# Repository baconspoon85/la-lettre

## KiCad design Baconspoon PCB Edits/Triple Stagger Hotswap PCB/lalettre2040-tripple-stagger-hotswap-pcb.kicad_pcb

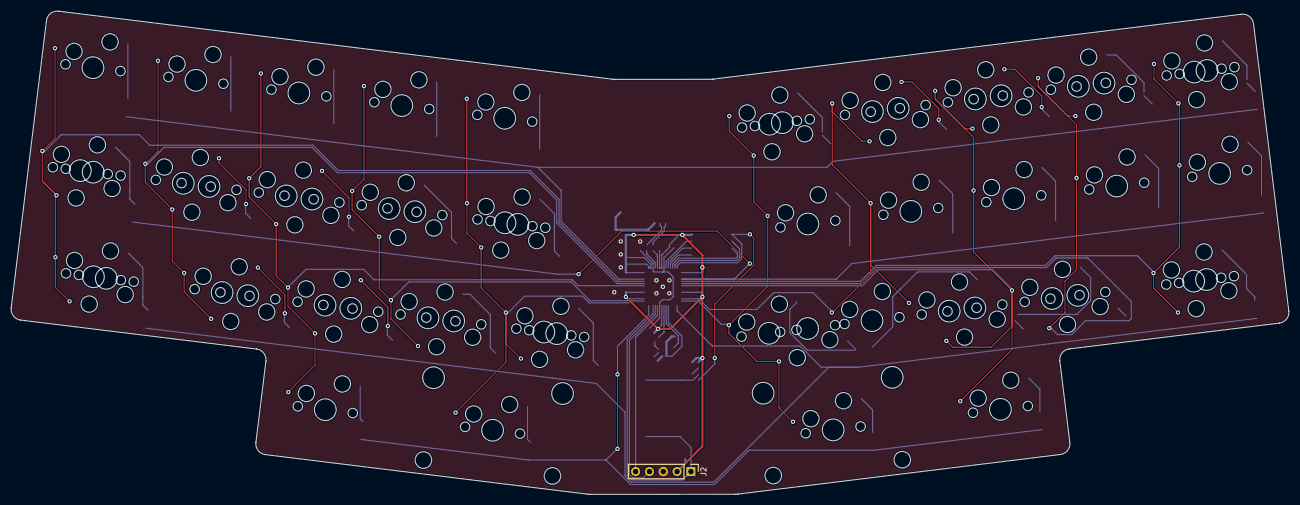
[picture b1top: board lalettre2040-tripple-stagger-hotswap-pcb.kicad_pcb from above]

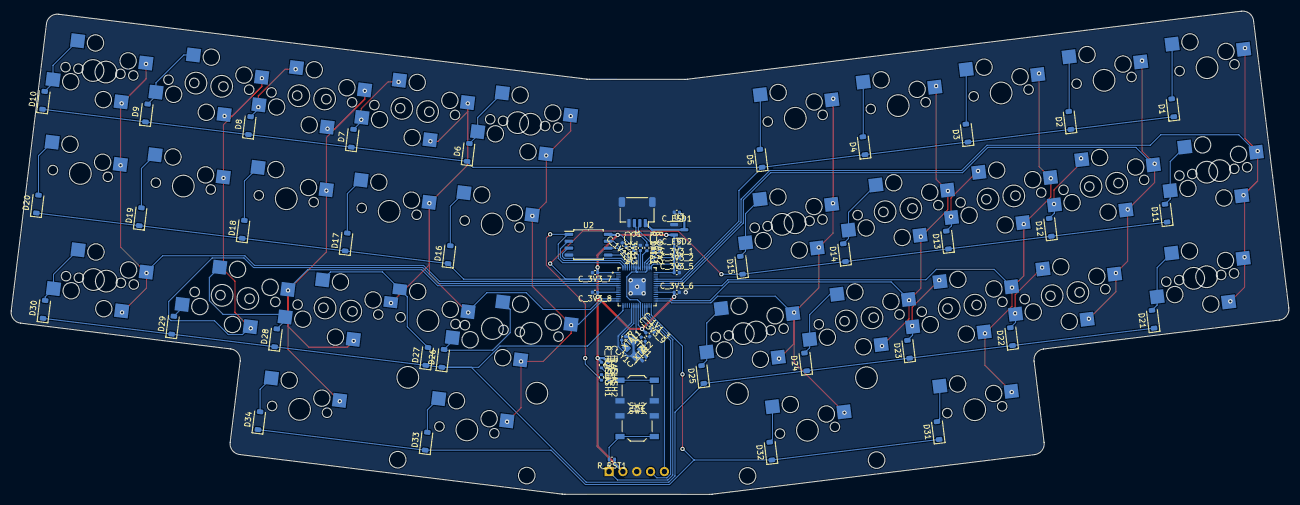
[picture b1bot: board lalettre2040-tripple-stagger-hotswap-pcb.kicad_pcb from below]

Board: 2 copper layers, 234.7 x 88.8 mm, 119 parts (65 on the bottom side), 70 nets.

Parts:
C_1V1_1, C_3V3_2: 1u; C_0402_1005Metric
C_1V1_2, C_1V1_3, C_3V3_3, C_3V3_4, C_3V3_5, C_3V3_6, C_3V3_7, C_3V3_8, C_3V3_9: 100n; C_0402_1005Metric
C_3V3_1: 10u; C_0402_1005Metric
C_ESD1, C_ESD2: 1u; C_0402_1005Metric
C_FLASH1: 100n; C_0402_1005Metric
C_XTAL1, C_XTAL2: 22p; C_0402_1005Metric
D1, D2, D3, D4, D5, D6, D7, D8, D9, D10, D11, D12, D13, D14, D15, D16, D17, D18, D19, D20, D21, D22, D23, D24, D25, D26, D27, D28, D29, D30, D31, D32, D33, D34: 1N4148W; D_SOD-123
J1: SM04B-SRSS-TB(LF)(SN); JST_SH_SM04B-SRSS-TB_1x04-1MP_P1.00mm_Horizontal
J2: SWD; PinHeader_1x05_P2.54mm_Vertical
MX1, MX2, MX3, MX4, MX5, MX6, MX7, MX8, MX9, MX11, MX12, MX13, MX14, MX15, MX16, MX17, MX18, MX19, MX20, MX22, MX23, MX24, MX26, MX27, MX28, MX29, MX34, MX36, MX37, MX38, MX39, MX41, MX42, MX43, MX46, MX47, MX48, MX49, MX51, MX52: CPG151101S11; MXOnly-1U-Hotswap
MX10, MX25, MX31, MX35, MX40, MX44: CPG151101S11; MXOnly-1.25U-Hotswap
MX21, MX53: CPG151101S11; MXOnly-1.5U-Hotswap
MX30, MX45, MX50: CPG151101S11; MXOnly-1.75U-Hotswap
MX32, MX33: CPG151101S11; MXOnly-2U-Hotswap-ReversedStabilizers
R_DATA1, R_DATA2: 27; R_0402_1005Metric
R_FLASH1: 1k; R_0402_1005Metric
R_FLASH2, R_FLASH3: 5k1; R_0402_1005Metric
R_RST1: 5k1; R_0402_1005Metric
R_XTAL1: 1k; R_0402_1005Metric
SW1: BOOTSEL; SW_SPST_TL3342
SW2: RESET; SW_SPST_TL3342
U1: RP2040; QFN40P700X700X90-57N
U2: W25Q128JVS; SOIC-8_5.23x5.23mm_P1.27mm
U3: XC6206P332MR; SOT-23
Y1: 12MHz; Crystal_SMD_3225-4Pin_3.2x2.5mm

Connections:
+: R_DATA1.2, U1.47 (USB_D+)
+1V1: C_1V1_1.1, C_1V1_2.1, C_1V1_3.1, U1.23 (DVDD), U1.45 (VREG_VOUT), U1.50 (DVDD)
+3V3: C_3V3_1.1, C_3V3_2.1, C_3V3_3.1, C_3V3_4.1, C_3V3_5.1, C_3V3_6.1, C_3V3_7.1, C_3V3_8.1, C_3V3_9.1, C_ESD2.1, C_FLASH1.1, J2.2, R_FLASH3.1, R_RST1.1, U1.1 (IOVDD), U1.10 (IOVDD), U1.22 (IOVDD), U1.33 (IOVDD), U1.42 (IOVDD), U1.43 (ADC_AVDD), U1.44 (VREG_IN), U1.48 (USB_VDD), U1.49 (IOVDD), U2.8 (VCC), U3.2 (VO)
+5V: C_ESD1.1, J1.1, U3.3 (VI)
-: R_DATA2.2, U1.46 (USB_D-)
CS: R_FLASH1.2, U1.56 (QSPI_SS), U2.1 (~CS)
D+: J1.3, R_DATA1.1
D-: J1.2, R_DATA2.1
GND: C_1V1_1.2, C_1V1_2.2, C_1V1_3.2, C_3V3_1.2, C_3V3_2.2, C_3V3_3.2, C_3V3_4.2, C_3V3_5.2, C_3V3_6.2, C_3V3_7.2, C_3V3_8.2, C_3V3_9.2, C_ESD1.2, C_ESD2.2, C_FLASH1.2, C_XTAL1.1, C_XTAL2.1, J1.4, J1.MP, J2.3, SW1.1, SW2.1, U1.19 (TESTEN), U1.57 (GND), U2.4 (GND), U3.1 (GND), Y1.2, Y1.4
unnamed: C_XTAL2.2, R_XTAL1.1, Y1.1
unnamed: D1.2 (A), MX1.2 (ROW)
unnamed: D2.2 (A), MX2.2 (ROW)
unnamed: D3.2 (A), MX3.2 (ROW)
unnamed: D4.2 (A), MX4.2 (ROW)
unnamed: D5.2 (A), MX5.2 (ROW)
unnamed: D6.2 (A), MX6.2 (ROW), MX35.2 (ROW)
unnamed: D7.2 (A), MX7.2 (ROW), MX36.2 (ROW)
unnamed: D8.2 (A), MX8.2 (ROW), MX37.2 (ROW)
unnamed: D9.2 (A), MX9.2 (ROW), MX38.2 (ROW)
unnamed: D10.2 (A), MX10.2 (ROW), MX39.2 (ROW)
unnamed: D11.2 (A), MX11.2 (ROW), MX40.2 (ROW)
unnamed: D12.2 (A), MX12.2 (ROW), MX41.2 (ROW)
unnamed: D13.2 (A), MX13.2 (ROW), MX42.2 (ROW)
unnamed: D14.2 (A), MX14.2 (ROW), MX43.2 (ROW)
unnamed: D15.2 (A), MX15.2 (ROW), MX44.2 (ROW)
unnamed: D16.2 (A), MX16.2 (ROW)
unnamed: D17.2 (A), MX17.2 (ROW)
unnamed: D18.2 (A), MX18.2 (ROW)
unnamed: D19.2 (A), MX19.2 (ROW)
unnamed: D20.2 (A), MX20.2 (ROW)
unnamed: D21.2 (A), MX21.2 (ROW), MX45.2 (ROW)
unnamed: D22.2 (A), MX22.2 (ROW), MX46.2 (ROW)
unnamed: D23.2 (A), MX23.2 (ROW), MX47.2 (ROW)
unnamed: D24.2 (A), MX24.2 (ROW), MX48.2 (ROW)
unnamed: D25.2 (A), MX25.2 (ROW), MX49.2 (ROW)
unnamed: D26.2 (A), MX26.2 (ROW), MX50.2 (ROW)
unnamed: D27.2 (A), MX27.2 (ROW), MX51.2 (ROW)
unnamed: D28.2 (A), MX28.2 (ROW), MX52.2 (ROW)
unnamed: D29.2 (A), MX29.2 (ROW)
unnamed: D30.2 (A), MX30.2 (ROW), MX53.2 (ROW)
unnamed: D31.2 (A), MX31.2 (ROW)
unnamed: D32.2 (A), MX32.2 (ROW)
unnamed: D33.2 (A), MX33.2 (ROW)
unnamed: D34.2 (A), MX34.2 (ROW)
unnamed: R_FLASH1.1, R_FLASH2.2, SW1.2
unnamed: R_FLASH2.1, R_FLASH3.2
QSPI_CLK: U1.52 (QSPI_SCLK), U2.6 (CLK)
RESET: J2.1, R_RST1.2, SW2.2, U1.26 (RUN)
SD0: U1.53 (QSPI_SD0), U2.5 (DI(IO0))
SD1: U1.55 (QSPI_SD1), U2.2 (DO(IO1))
SD2: U1.54 (QSPI_SD2), U2.3 (IO2)
SD3: U1.51 (QSPI_SD3), U2.7 (IO3)
SWCLK: J2.5, U1.24 (SWCLK)
SWDIO: J2.4, U1.25 (SWD)
XTAL_IN: C_XTAL1.2, U1.20 (XIN), Y1.3
XTAL_OUT: R_XTAL1.2, U1.21 (XOUT)
col0: MX1.1 (COL), MX11.1 (COL), MX21.1 (COL), MX40.1 (COL), MX45.1 (COL), U1.38 (GPIO26_ADC0)
col1: MX2.1 (COL), MX12.1 (COL), MX22.1 (COL), MX41.1 (COL), MX46.1 (COL), U1.37 (GPIO25)
col2: MX3.1 (COL), MX13.1 (COL), MX23.1 (COL), MX31.1 (COL), MX42.1 (COL), MX47.1 (COL), U1.36 (GPIO24)
col3: MX4.1 (COL), MX14.1 (COL), MX24.1 (COL), MX43.1 (COL), MX48.1 (COL), U1.30 (GPIO19)
col4: MX5.1 (COL), MX15.1 (COL), MX25.1 (COL), MX32.1 (COL), MX44.1 (COL), MX49.1 (COL), U1.29 (GPIO18)
col5: MX6.1 (COL), MX16.1 (COL), MX26.1 (COL), MX33.1 (COL), MX35.1 (COL), MX50.1 (COL), U1.14 (GPIO11)
col6: MX7.1 (COL), MX17.1 (COL), MX27.1 (COL), MX36.1 (COL), MX51.1 (COL), U1.13 (GPIO10)
col7: MX8.1 (COL), MX18.1 (COL), MX28.1 (COL), MX34.1 (COL), MX37.1 (COL), MX52.1 (COL), U1.7 (GPIO5)
col8: MX9.1 (COL), MX19.1 (COL), MX29.1 (COL), MX38.1 (COL), U1.6 (GPIO4)
col9: MX10.1 (COL), MX20.1 (COL), MX30.1 (COL), MX39.1 (COL), MX53.1 (COL), U1.5 (GPIO3)
row0: D1.1 (K), D2.1 (K), D3.1 (K), D4.1 (K), D5.1 (K), D6.1 (K), D7.1 (K), D8.1 (K), D9.1 (K), D10.1 (K), U1.39 (GPIO27_ADC1)
row1: D11.1 (K), D12.1 (K), D13.1 (K), D14.1 (K), D15.1 (K), D16.1 (K), D17.1 (K), D18.1 (K), D19.1 (K), D20.1 (K), U1.4 (GPIO2)
row2: D21.1 (K), D22.1 (K), D23.1 (K), D24.1 (K), D25.1 (K), D26.1 (K), D27.1 (K), D28.1 (K), D29.1 (K), D30.1 (K), U1.15 (GPIO12)
row3: D31.1 (K), D32.1 (K), D33.1 (K), D34.1 (K), U1.28 (GPIO17)

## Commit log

2024-02-11 Initial commit of baconspoon case and PCB (La Cuillère) edits.
2024-02-12 Add silks to PCB and flipped hotswaps to back. Add readme.
2024-02-12 Renamed PCB files and dded fabrication files.
2024-02-16 Updated README and updated case files with magnet closure model.
2024-04-07 update read me and add case, pcb, and firmware
2024-04-08 correct holes in case bottom
2024-04-08 add drawings - threded hole notes
2024-04-08 added SWD header recess to plate models to avoid shorting solder pads with conductive plate materials
